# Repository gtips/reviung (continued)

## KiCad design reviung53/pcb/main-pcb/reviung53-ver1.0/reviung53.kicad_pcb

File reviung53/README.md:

# REVIUNG53  

The REVIUNG53 is 53-key keyboard.  

## Parts list  

PCB --- 1 piece  
Top plate [PCB] --- 1  
Bottom plate --- 1 piece  
Spacer 7mm --- 10 pieces  
M2 screw 4mm --- 16 pcs  
M2 screw 12mm --- 6 pcs  
M2 nut --- 2 pcs  
Rubber feet --- 6 pieces  
Diode [1N4148 SMD] --- 53 pieces  
PCB socket for switch --- 54 pcs  
Tact switch --- 1 piece  
LED [WS2812B] --- 10 pieces  
Stabilizer --- 2U x 2 , 6.25U x 1 ~  2U x 5  

ProMicro --- 1  
Con through (spring pin header 12P) --- 2  
MX compatible key switch --- 53 pcs ~ 49 (Minimum)  
MX compatible keycapset
MicroUSB cable --- 1  

### Option (Middle acrylic plate ver)
Hi-Pro acrylic frame --- 1  
Middle acrylic plate (top) --- 1  
Middle acrylic plate (bottom) --- 1  
Silicon sheet --- 1 sheet  
M2 screw 12mm --- 10 pcs  
  
[Firmware](https://github.com/qmk/qmk_firmware/tree/master/keyboards/reviung/reviung53)  
[Build guide](https://reviung.com/build-guide/)

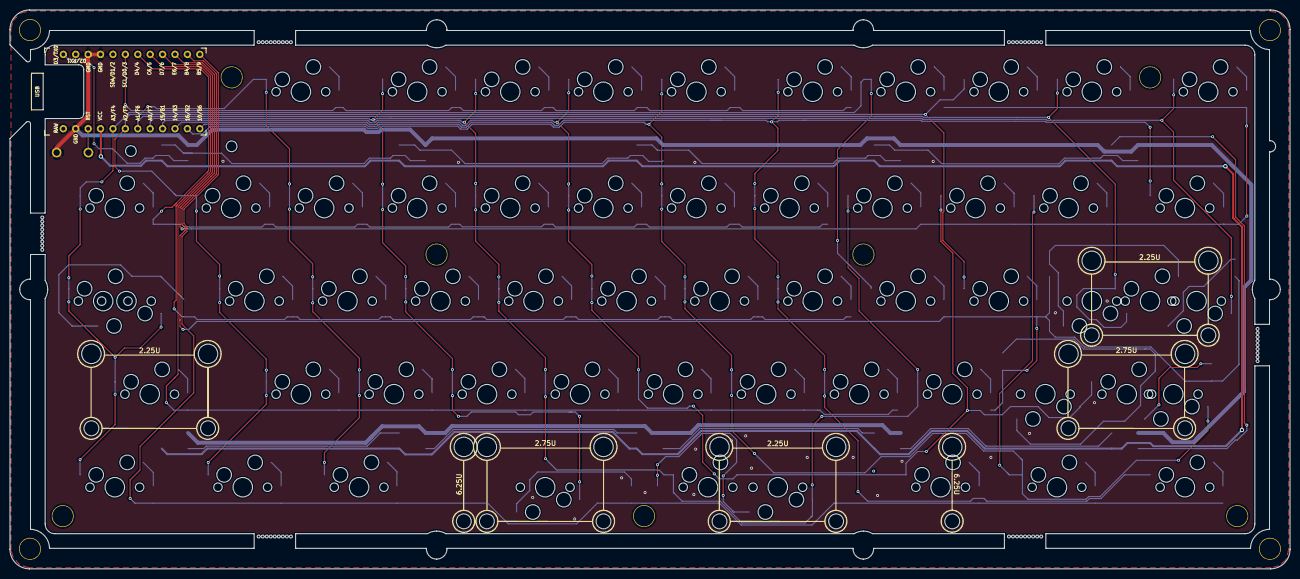
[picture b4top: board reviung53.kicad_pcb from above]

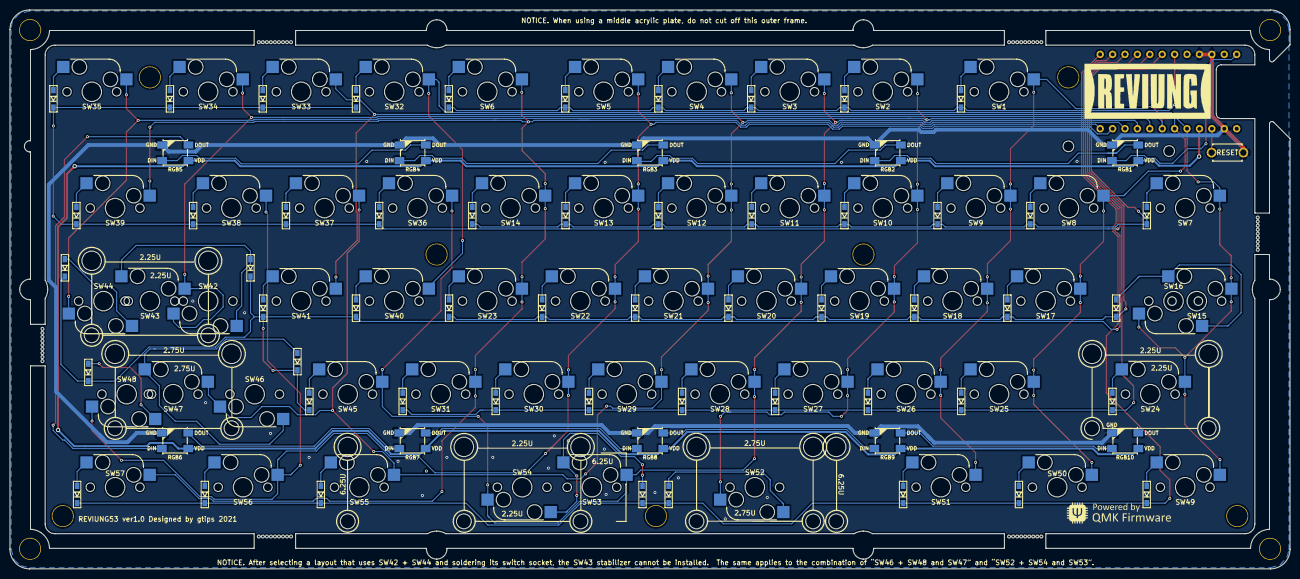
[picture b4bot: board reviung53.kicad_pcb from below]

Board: 2 copper layers, 262.0 x 114.4 mm, 130 parts (64 on the bottom side), 81 nets.

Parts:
D1, D2, D3, D4, D5, D6, D7, D8, D9, D10, D11, D12, D13, D14, D15, D16, D17, D18, D19, D20, D21, D22, D23, D24, D25, D26, D27, D28, D29, D30, D31, D32, D33, D34, D35, D36, D37, D38, D39, D40, D41, D42, D43, D44, D45, D46, D47, D48, D49, D50, D51, D52, D53: 1N4148W; D3_SMD_1side
RESET1: SW_PUSH; ResetSW_1side
RGB1, RGB2, RGB3, RGB4, RGB5, RGB6, RGB7, RGB8, RGB9, RGB10: WS2812B; LED_WS2812B_PLCC4_5.0x5.0mm_P3.2mm_BigFoot
Ref**: Val**; HOLE_2.2mm
Ref**#2: Val**; HOLE_2.2mm
SW1: 1; MXOnly-1U-Hotswap
SW2: 2; MXOnly-1U-Hotswap
SW3: 3; MXOnly-1U-Hotswap
SW4: 4; MXOnly-1U-Hotswap
SW5: 5; MXOnly-1U-Hotswap
SW6: 6; MXOnly-1U-Hotswap
SW7, SW39, SW49, SW57: 1.5U; MXOnly-1.5U-Hotswap
SW8: Q; MXOnly-1U-Hotswap
SW9: W; MXOnly-1U-Hotswap
SW10: E; MXOnly-1U-Hotswap
SW11: R; MXOnly-1U-Hotswap
SW12: T; MXOnly-1U-Hotswap
SW13: Y; MXOnly-1U-Hotswap
SW14: U; MXOnly-1U-Hotswap
SW15, SW44, SW50, SW51, SW55, SW56: 1.25U; MXOnly-1.25U-Hotswap
SW16, SW48: 1.75U; MXOnly-1.75U-Hotswap
SW17: A; MXOnly-1U-Hotswap
SW18: S; MXOnly-1U-Hotswap
SW19: D; MXOnly-1U-Hotswap
SW20: F; MXOnly-1U-Hotswap
SW21: G; MXOnly-1U-Hotswap
SW22: H; MXOnly-1U-Hotswap
SW23: J; MXOnly-1U-Hotswap
SW24, SW43: 2.25U; MXOnly-2.25U-Hotswap-ReversedStabilizers
SW25: Z; MXOnly-1U-Hotswap
SW26: X; MXOnly-1U-Hotswap
SW27: C; MXOnly-1U-Hotswap
SW28: V; MXOnly-1U-Hotswap
SW29: B; MXOnly-1U-Hotswap
SW30: N; MXOnly-1U-Hotswap
SW31: M; MXOnly-1U-Hotswap
SW32: 7; MXOnly-1U-Hotswap
SW33: 8; MXOnly-1U-Hotswap
SW34: 9; MXOnly-1U-Hotswap
SW35, SW37: 0; MXOnly-1U-Hotswap
SW36: I; MXOnly-1U-Hotswap
SW38: P; MXOnly-1U-Hotswap
SW40: K; MXOnly-1U-Hotswap
SW41: L; MXOnly-1U-Hotswap
SW42, SW46: 1U; MXOnly-1U-Hotswap
SW45: <; MXOnly-1U-Hotswap
SW47: 2.75U; MXOnly-2.75U-Hotswap-ReversedStabilizers
SW52: 2.75U; MXOnly-2.75U-Hotswap
SW53: 6.25U; MXOnly-6.25U-Hotswap-ReversedStabilizers
SW54: 2.25U; MXOnly-2.25U-Hotswap
U1: ProMicro
breakaway: Stamp_Holes_7.5mm
breakaway#2, breakaway#3, breakaway#4, breakaway#5, breakaway#6: Stamp_Holes_7.5mm

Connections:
GND: RESET1.2, RGB1.3, RGB2.3, RGB3.3, RGB4.3, RGB5.3, RGB6.3, RGB7.3, RGB8.3, RGB9.3, RGB10.3, U1.3, U1.4, U1.23
LED: RGB1.4, U1.1
unnamed: D1.2, SW1.2
unnamed: D2.2, SW2.2
unnamed: D3.2, SW3.2
unnamed: D4.2, SW4.2
unnamed: D5.2, SW5.2
unnamed: D6.2, SW6.2
unnamed: D7.2, SW7.2
unnamed: D8.2, SW8.2
unnamed: D9.2, SW9.2
unnamed: D10.2, SW10.2
unnamed: D11.2, SW11.2
unnamed: D12.2, SW12.2
unnamed: D13.2, SW13.2
unnamed: D14.2, SW14.2
unnamed: D15.2, SW17.2
unnamed: D16.2, SW18.2
unnamed: D17.2, SW19.2
unnamed: D18.2, SW20.2
unnamed: D19.2, SW21.2
unnamed: D20.2, SW22.2
unnamed: D21.2, SW23.2
unnamed: D22.2, SW15.2, SW16.2
unnamed: D23.2, SW24.2
unnamed: D24.2, SW25.2
unnamed: D25.2, SW26.2
unnamed: D26.2, SW27.2
unnamed: D27.2, SW28.2
unnamed: D28.2, SW29.2
unnamed: D29.2, SW30.2
unnamed: D30.2, SW31.2
unnamed: D31.2, SW32.2
unnamed: D32.2, SW33.2
unnamed: D33.2, SW34.2
unnamed: D34.2, SW35.2
unnamed: D35.2, SW36.2
unnamed: D36.2, SW37.2
unnamed: D37.2, SW38.2
unnamed: D38.2, SW39.2
unnamed: D39.2, SW40.2
unnamed: D40.2, SW41.2
unnamed: D41.2, SW44.2
unnamed: D42.2, SW45.2
unnamed: D43.2, SW48.2
unnamed: D44.2, SW42.2, SW43.2
unnamed: D45.2, SW46.2, SW47.2
unnamed: D46.2, SW49.2
unnamed: D47.2, SW50.2
unnamed: D48.2, SW51.2
unnamed: D49.2, SW52.2
unnamed: D50.2, SW55.2
unnamed: D51.2, SW56.2
unnamed: D52.2, SW57.2
unnamed: D53.2, SW53.2, SW54.2
unnamed: RGB1.2, RGB2.4
unnamed: RGB2.2, RGB3.4
unnamed: RGB3.2, RGB4.4
unnamed: RGB4.2, RGB5.4
unnamed: RGB5.2, RGB6.4
unnamed: RGB6.2, RGB7.4
unnamed: RGB7.2, RGB8.4
unnamed: RGB8.2, RGB9.4
unnamed: RGB9.2, RGB10.4
VCC: RGB1.1, RGB2.1, RGB3.1, RGB4.1, RGB5.1, RGB6.1, RGB7.1, RGB8.1, RGB9.1, RGB10.1, U1.21
col0: SW7.1, SW15.1, SW16.1, SW24.1, SW32.1, SW40.1, SW49.1, U1.20
col1: SW8.1, SW17.1, SW25.1, SW33.1, SW41.1, SW50.1, U1.19
col2: SW1.1, SW9.1, SW18.1, SW26.1, SW34.1, SW42.1, SW43.1, SW51.1, U1.18
col3: SW2.1, SW10.1, SW19.1, SW27.1, SW35.1, SW44.1, SW52.1, U1.17
col4: SW3.1, SW11.1, SW20.1, SW28.1, SW36.1, SW45.1, SW53.1, SW54.1, U1.16
col5: SW4.1, SW12.1, SW21.1, SW29.1, SW37.1, SW46.1, SW47.1, SW55.1, U1.15
col6: SW5.1, SW13.1, SW22.1, SW30.1, SW38.1, SW48.1, SW56.1, U1.14
col7: SW6.1, SW14.1, SW23.1, SW31.1, SW39.1, SW57.1, U1.13
reset: RESET1.1, U1.22
row0: D1.1, D2.1, D3.1, D4.1, D5.1, D6.1, U1.6
row1: D7.1, D8.1, D9.1, D10.1, D11.1, D12.1, D13.1, D14.1, U1.7
row2: D15.1, D16.1, D17.1, D18.1, D19.1, D20.1, D21.1, D22.1, U1.8
row3: D23.1, D24.1, D25.1, D26.1, D27.1, D28.1, D29.1, D30.1, U1.9
row4: D31.1, D32.1, D33.1, D34.1, D35.1, D36.1, D37.1, D38.1, U1.10
row5: D39.1, D40.1, D41.1, D42.1, D43.1, D44.1, D45.1, U1.11
row6: D46.1, D47.1, D48.1, D49.1, D50.1, D51.1, D52.1, D53.1, U1.12

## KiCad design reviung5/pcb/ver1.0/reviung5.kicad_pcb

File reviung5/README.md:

# REVIUNG5  

The REVIUNG5 is 5-key (or 4-key + Rotary Encoder) macropad.  

## Parts list  

| Qnty | Parts | Description |
| --- | --- | --- |
| 1 | PCB | Main PCB |  
| 1 | Top plate |  |
| 1 | Bottom plate |  |
| 1 | ProMicro cover plate | option |
| 3 | Acrylic spacer |  for Pro Micro cover |
| 3 | Spacer | for body |
| 6 | M2 screw 4mm |  for body |  
| 3 | M2 screw 8 - 10mm |  for Pro Micro cover |
| 3 | M2 nut |  for Pro Micro cover |
| 4 | Rubber feet |  |
| 5 | Diode [1N4148]  |  |
| 1 | Tact switch |  RESET switch |
| 4 | LED [WS2812B]  | option |
| - | - | - |
| 1 | ProMicro |  |
| 2 | Con through  | or spring pin header 12P |
| 5 (or 4) | MX compatible key switch |  |  
| 5 (or 4) | MX compatible keycap (1U) |  | 
| 1 (or 0) | Rotary Encoder | Alps EC12 series compatible | 
| 1 | MicroUSB cable |  |
  
[Firmware](https://github.com/qmk/qmk_firmware/tree/master/keyboards/reviung/reviung5)  
[Build guide](https://reviung.com/build-guide/)

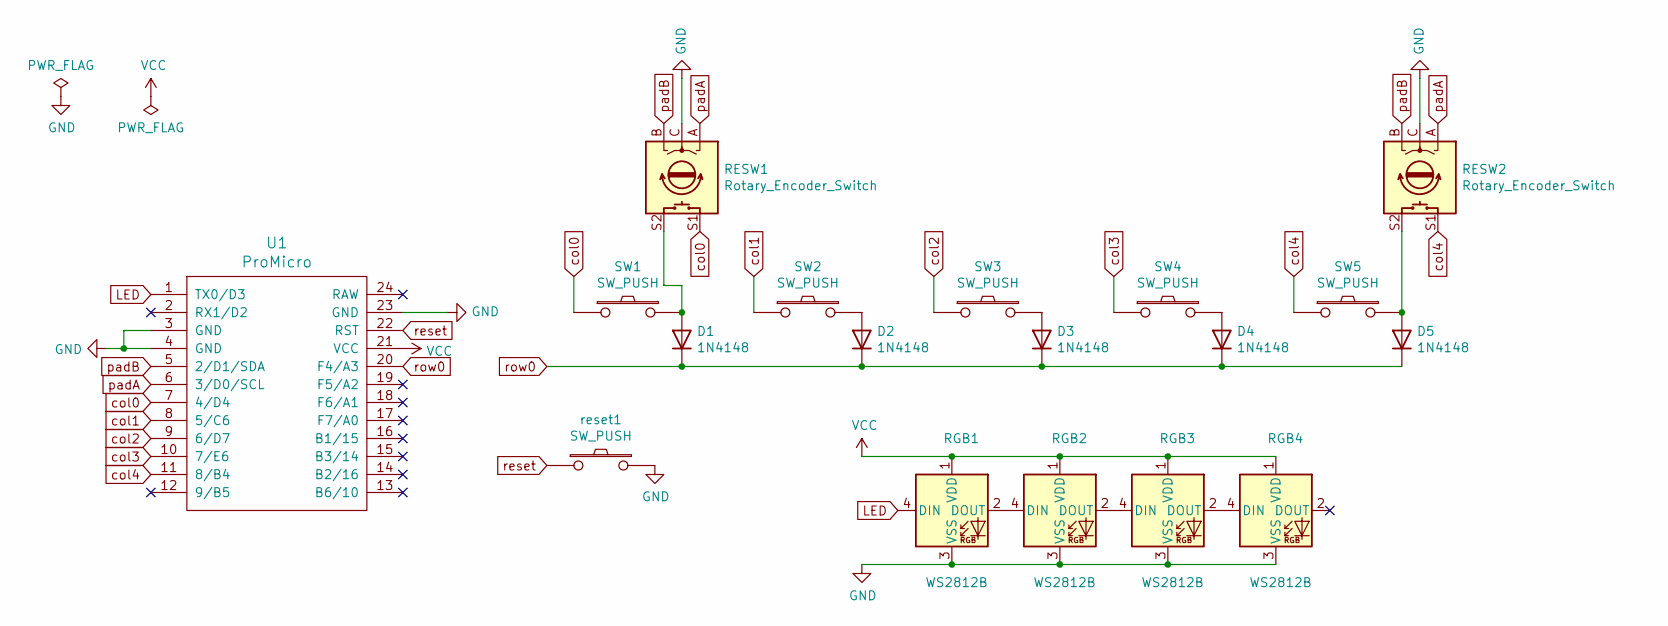
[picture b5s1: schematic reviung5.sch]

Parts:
D1, D2, D3, D4, D5: 1N4148; D3_TH_SMD_1side
RESW1, RESW2: Rotary_Encoder_Switch; RotaryEncoder_Alps_EC12E-Switch_Vertical_H20mm_CircularMoun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
RGB1, RGB2, RGB3, RGB4: WS2812B; LED_WS2812B_PLCC4_5.0x5.0mm_P3.2mm
SW1, SW5: SW_PUSH; MXOnly-1U-3pin
SW2, SW3, SW4: SW_PUSH; MXOnly-1U-NoLED
U1: ProMicro
reset1: SW_PUSH; ResetSW_TH_SMD

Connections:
GND: RESW1.C, RESW2.C, RGB1.3 (VSS), RGB2.3 (VSS), RGB3.3 (VSS), RGB4.3 (VSS), U1.3 (GND), U1.4 (GND), U1.23 (GND), reset1.2
LED: RGB1.4 (DIN), U1.1 (TX0/D3)
unnamed: D1.2 (A), RESW1.S2, SW1.2
unnamed: D2.2 (A), SW2.2
unnamed: D3.2 (A), SW3.2
unnamed: D4.2 (A), SW4.2
unnamed: D5.2 (A), RESW2.S2, SW5.2
unnamed: RGB1.2 (DOUT), RGB2.4 (DIN)
unnamed: RGB2.2 (DOUT), RGB3.4 (DIN)
unnamed: RGB3.2 (DOUT), RGB4.4 (DIN)
VCC: RGB1.1 (VDD), RGB2.1 (VDD), RGB3.1 (VDD), RGB4.1 (VDD), U1.21 (VCC)
col0: RESW1.S1, SW1.1, U1.7 (4/D4)
col1: SW2.1, U1.8 (5/C6)
col2: SW3.1, U1.9 (6/D7)
col3: SW4.1, U1.10 (7/E6)
col4: RESW2.S1, SW5.1, U1.11 (8/B4)
padA: RESW1.A, RESW2.A, U1.6 (3/D0/SCL)
padB: RESW1.B, RESW2.B, U1.5 (2/D1/SDA)
reset: U1.22 (RST), reset1.1
row0: D1.1 (K), D2.1 (K), D3.1 (K), D4.1 (K), D5.1 (K), U1.20 (F4/A3)

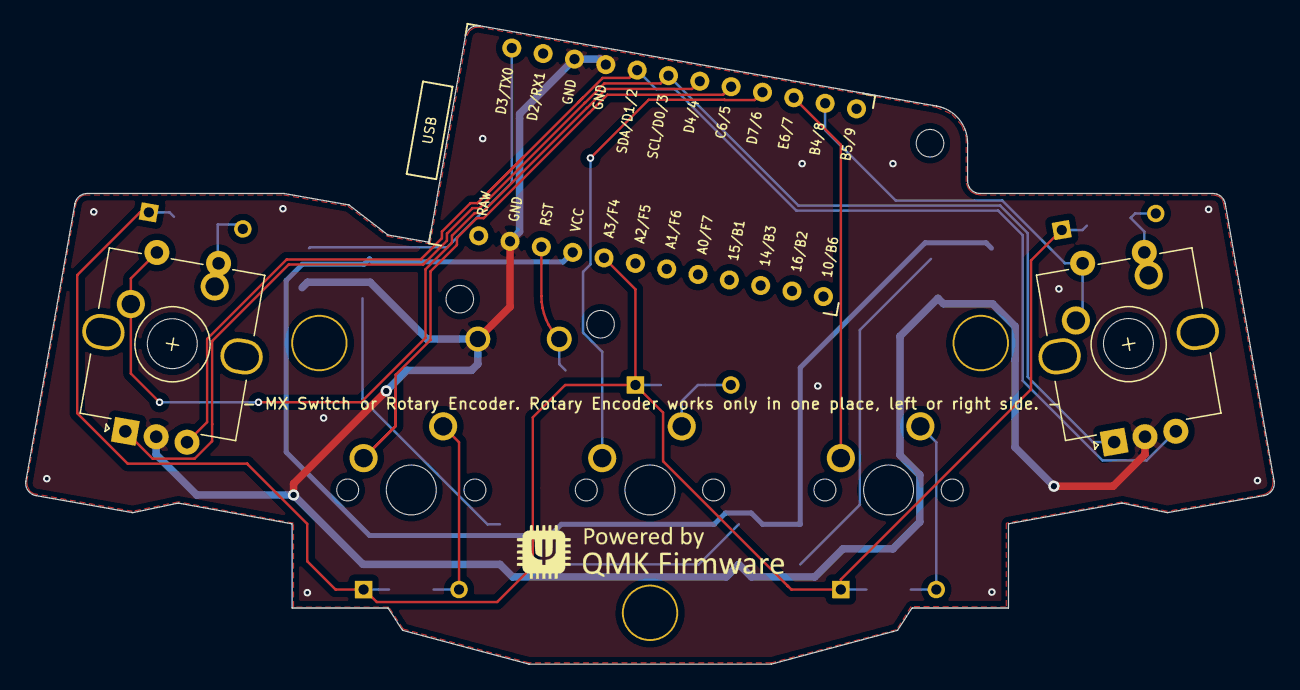
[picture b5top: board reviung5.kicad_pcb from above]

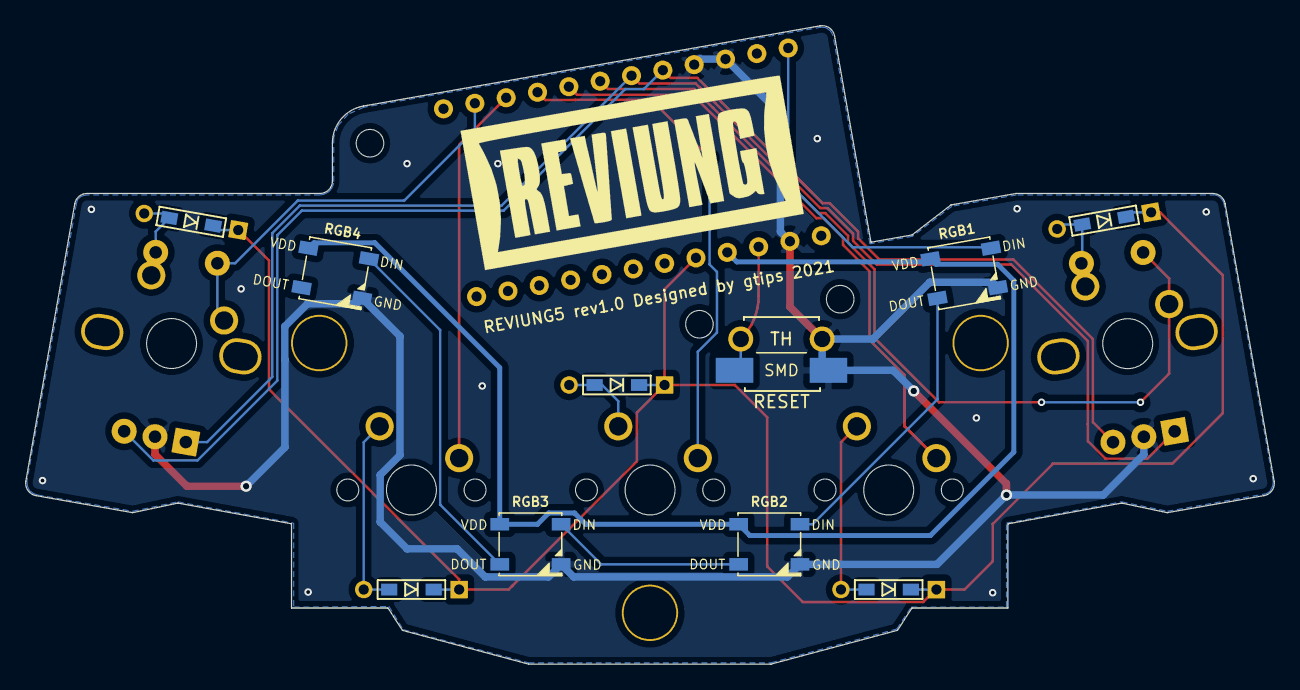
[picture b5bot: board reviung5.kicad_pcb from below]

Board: 2 copper layers, 99.7 x 51.0 mm, 21 parts (10 on the bottom side), 20 nets.

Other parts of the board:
Ref**: Val**; HOLE_2.2mm
Ref**#2, Ref**#3: Val**; HOLE_2.2mm

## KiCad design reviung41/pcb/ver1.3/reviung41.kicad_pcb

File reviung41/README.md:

# REVIUNG41  

The REVIUNG41 is 41-key column staggered keyboard.  

## Parts list  

PCB --- 1 piece  
Top plate [PCB] --- 1  
Silicon sheet --- 1 sheet  
Middle acrylic plate (top) --- 1  
Middle acrylic plate (bottom) --- 1  
Bottom plate --- 1 piece  
ProMicro protective plate --- 4 types  
Acrylic spacer --- 3 pieces  
Spacer --- 11 pieces  
M2 screw 4mm --- 22 pcs  
M2 screw 10mm --- 3 pcs  
M2 nut --- 3 pcs  
Rubber feet --- 6 pieces  
Diode [1N4148 SMD] --- 41 pieces  
PCB socket for switch --- 41 pcs  
Tact switch --- 1 piece  
LED [WS2812B] --- 11 pieces  
Stabilizer --- 1 piece  

ProMicro --- 1  
Con through (spring pin header 12P) --- 2  
MX compatible key switch --- 41 pcs  
MX compatible keycap (1U) --- 36  
Keycap (2.25U or 2U) --- 1  
Keycap (1.25U or 1U) --- 4  
MicroUSB cable --- 1  
  
[Firmware](https://github.com/qmk/qmk_firmware/tree/master/keyboards/reviung/reviung41)  
[Build guide](https://reviung.com/build-guide/391/)

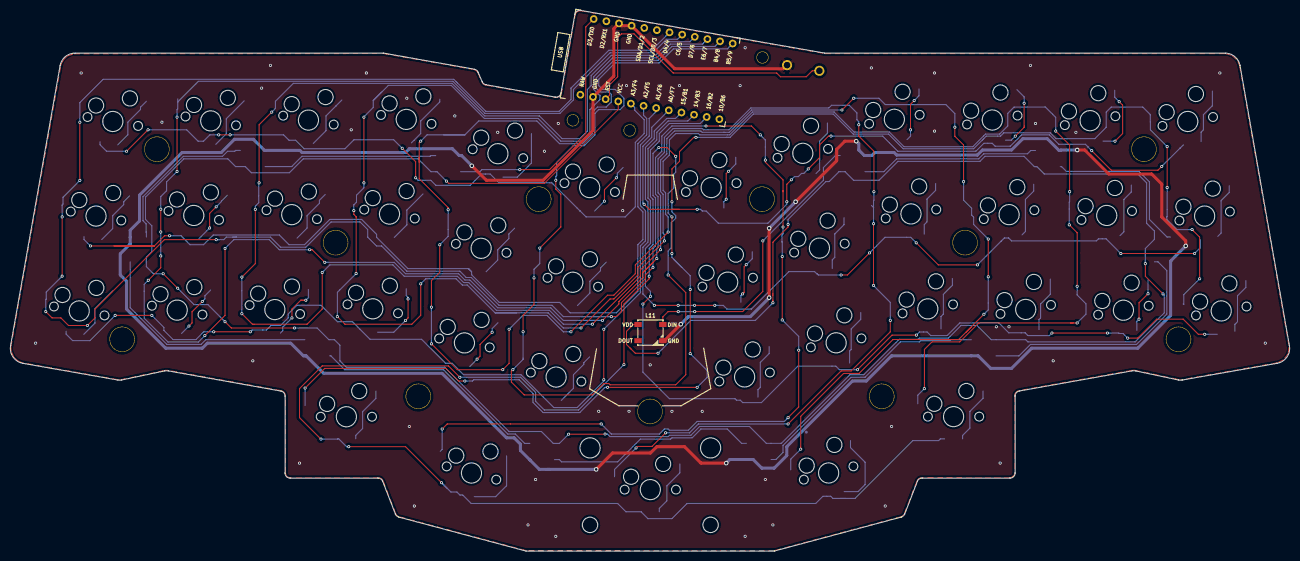
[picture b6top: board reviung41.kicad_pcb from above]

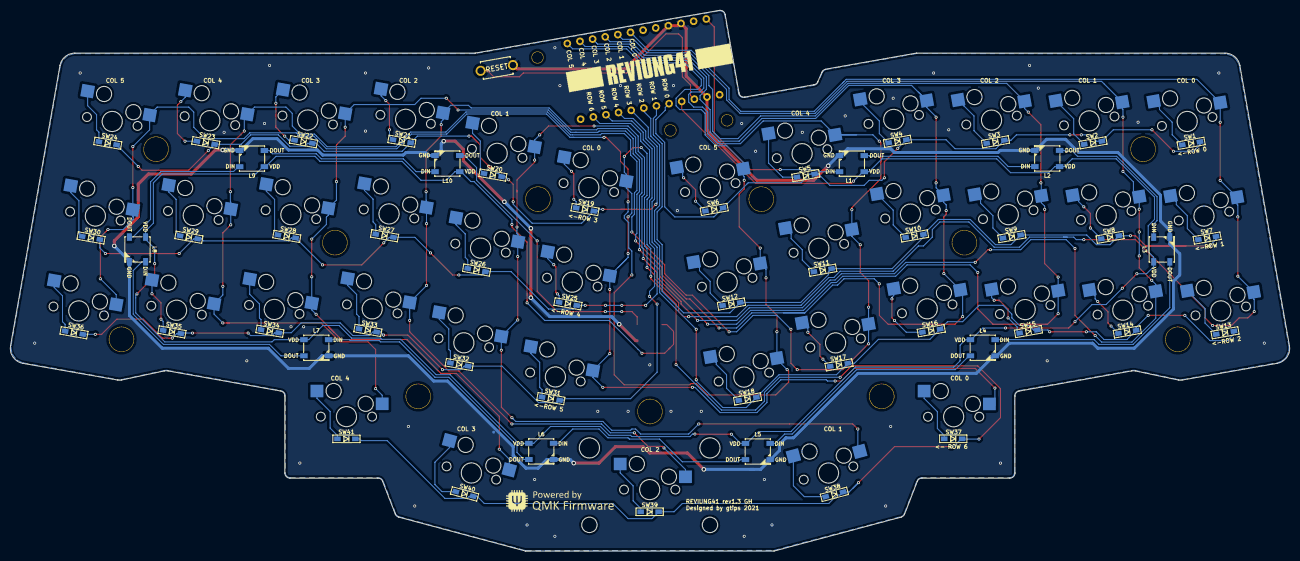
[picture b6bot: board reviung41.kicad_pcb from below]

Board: 2 copper layers, 253.3 x 107.1 mm, 109 parts (52 on the bottom side), 68 nets.

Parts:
D1, D2, D3, D4, D5, D6, D7, D8, D9, D10, D11, D12, D13, D14, D15, D16, D17, D18, D19, D20, D21, D22, D23, D24, D25, D26, D27, D28, D29, D30, D31, D32, D33, D34, D35, D36, D37, D38, D39, D40, D41: 1N4148W; D3_SMD_1side
H1: H1; HOLE
H2: H2; HOLE
H3: H3; HOLE
H4: H4; HOLE
H5: H5; HOLE
H6: H6; HOLE
H7: H7; HOLE
H8: H8; HOLE
H9: H9; HOLE
H10: H10; HOLE
H11: H11; HOLE
H12: H12; HOLE_2.2mm
H13: H13; HOLE_2.2mm
H14: H14; HOLE_2.2mm
L1, L2, L3, L4, L5, L6, L7, L8, L9, L10, L11: WS2812B; LED_WS2812B_PLCC4_5.0x5.0mm_P3.2mm
RESET1: SW_PUSH; ResetSW_1side
SW1, SW2, SW3, SW4, SW5, SW6, SW7, SW8, SW9, SW10, SW11, SW12, SW13, SW14, SW15, SW16, SW17, SW18, SW19, SW20, SW21, SW22, SW23, SW24, SW25, SW26, SW27, SW28, SW29, SW30, SW31, SW32, SW33, SW34, SW35, SW36, SW37, SW38, SW40, SW41: SW_PUSH; MXOnly-1U-Hotswap
SW39: SW_2U_PUSH; MXOnly-2U-Hotswap-ReversedStabilizers
U1: ProMicro

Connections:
GND: L1.3, L2.3, L3.3, L4.3, L5.3, L6.3, L7.3, L8.3, L9.3, L10.3, L11.3, RESET1.2, U1.3, U1.4, U1.23
LED: L1.4, U1.1
unnamed: D1.2, SW1.2
unnamed: D2.2, SW2.2
unnamed: D3.2, SW3.2
unnamed: D4.2, SW4.2
unnamed: D5.2, SW5.2
unnamed: D6.2, SW6.2
unnamed: D7.2, SW7.2
unnamed: D8.2, SW8.2
unnamed: D9.2, SW9.2
unnamed: D10.2, SW10.2
unnamed: D11.2, SW11.2
unnamed: D12.2, SW12.2
unnamed: D13.2, SW13.2
unnamed: D14.2, SW14.2
unnamed: D15.2, SW15.2
unnamed: D16.2, SW16.2
unnamed: D17.2, SW17.2
unnamed: D18.2, SW18.2
unnamed: D19.2, SW19.2
unnamed: D20.2, SW20.2
unnamed: D21.2, SW21.2
unnamed: D22.2, SW22.2
unnamed: D23.2, SW23.2
unnamed: D24.2, SW24.2
unnamed: D25.2, SW25.2
unnamed: D26.2, SW26.2
unnamed: D27.2, SW27.2
unnamed: D28.2, SW28.2
unnamed: D29.2, SW29.2
unnamed: D30.2, SW30.2
unnamed: D31.2, SW31.2
unnamed: D32.2, SW32.2
unnamed: D33.2, SW33.2
unnamed: D34.2, SW34.2
unnamed: D35.2, SW35.2
unnamed: D36.2, SW36.2
unnamed: D37.2, SW37.2
unnamed: D38.2, SW38.2
unnamed: D39.2, SW39.2
unnamed: D40.2, SW40.2
unnamed: D41.2, SW41.2
unnamed: L1.2, L2.4
unnamed: L2.2, L3.4
unnamed: L3.2, L4.4
unnamed: L4.2, L5.4
unnamed: L5.2, L6.4
unnamed: L6.2, L7.4
unnamed: L7.2, L8.4
unnamed: L8.2, L9.4
unnamed: L10.2, L11.4
unnamed: L9.2, L10.4
VCC: L1.1, L2.1, L3.1, L4.1, L5.1, L6.1, L7.1, L8.1, L9.1, L10.1, L11.1, U1.21
col0: SW1.1, SW7.1, SW13.1, SW19.1, SW25.1, SW31.1, SW37.1, U1.7
col1: SW2.1, SW8.1, SW14.1, SW20.1, SW26.1, SW32.1, SW38.1, U1.8
col2: SW3.1, SW9.1, SW15.1, SW21.1, SW27.1, SW33.1, SW39.1, U1.9
col3: SW4.1, SW10.1, SW16.1, SW22.1, SW28.1, SW34.1, SW40.1, U1.10
col4: SW5.1, SW11.1, SW17.1, SW23.1, SW29.1, SW35.1, SW41.1, U1.11
col5: SW6.1, SW12.1, SW18.1, SW24.1, SW30.1, SW36.1, U1.12
reset: RESET1.1, U1.22
row0: D1.1, D2.1, D3.1, D4.1, D5.1, D6.1, U1.20
row1: D7.1, D8.1, D9.1, D10.1, D11.1, D12.1, U1.19
row2: D13.1, D14.1, D15.1, D16.1, D17.1, D18.1, U1.18
row3: D19.1, D20.1, D21.1, D22.1, D23.1, D24.1, U1.17
row4: D25.1, D26.1, D27.1, D28.1, D29.1, D30.1, U1.16
row5: D31.1, D32.1, D33.1, D34.1, D35.1, D36.1, U1.15
row6: D37.1, D38.1, D39.1, D40.1, D41.1, U1.14

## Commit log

2019-07-12 add: pcb
2019-08-27 add pcb, svg and image
2019-09-25 add reviung39/pcb-top-plate/gerber.zip
2019-09-25 add reviung34split
2019-09-30 add reviung34split/image/REVIUNG34.jpg
2019-09-30 add reviung34split/README.md
2019-11-12 update reviung34split pcb file
2019-12-05 add reviung39/acrylic-plate/ and reviung39s/acrylic-plate/
2019-12-12 add reviung39/acrylic-plate/lower-middle-plate/README.md
2019-12-12 add reviung39/image/REVIUNG39mdp-x.jpg
2019-12-14 add reviung39/acrylic-plate.zip
2020-01-06 add reviung41
2020-01-21 update reviung41/acrylic-plate/upper-middle-plate/reviung41-upper-middle-plate
2020-02-09 add reviung41/image/ some images
2020-02-13 add README.md
2020-02-13 reviung41/image/reviung41-07.jpg, reviung41-08.jpg
2020-03-04 add reviung-stand
2020-03-04 update reviung-stand files
2020-07-16 add reviung61
2020-07-16 update reviung61/pcb-top-plate-ALPS/
2020-08-24 remove REVIUNG-STAND
2020-08-25 add reviung33
2020-08-25 upodate /README.md
2020-08-25 update reviung/acrylic-plate/
2020-08-27 add reviung39Mk-II
2020-11-13 add REVIUNG34 Mk-II
2021-01-05 Adding 3d model and stl for reviung39Mkii case
2021-04-19 add reviung41 top and bottom plate files
2021-04-19 add reviung41 top plate dwg file
2021-04-25 add new reviung34
2021-04-25 add gerver_r34_v1.zip
2021-04-26 add reviung34/acrylic-plate/bottom-plate/reviung34-bottom-plate-2mm-ver1.dxf
2021-04-28 Create fr4 bottom plate for reviung41
2021-05-04 fix README.md
2021-05-25 update reviung39_Mk-II/acrylic-plate/
2021-05-25 update reviung34/acrylic-plate/
2021-05-25 update reviung41/acrylic-plate/
2021-05-25 update reviung41/pcb/ver1.3 and reviung41/pcb-top-plate/ver1.3/
2021-06-29 fix reviung5/README.md
2021-11-15 Fix link to reviung39 mk-II in readme
    Minor tweak to documentation.
2021-12-02 add: reviung53/
2021-12-03 add: reviung53/acrylic-plate/mcu-cover-ver1.0/
2021-12-06 add: reviung53/acrylic-plate/for-middle-plate/, /for-stacked-acrylic-case/
2021-12-08 renamed folder name
2022-01-20 add reviung53/acrylic-plate/for-stacked-acrylic-case/Assembly_drawing.jpg
2022-01-20 Fixed for-middle-plate directory name
2022-01-20 fixed README.md
2022-03-31 RJ45_NONAME_8P8C_Horizontal
    Redone with very common RJ45_NONAME_8P8C_Horizontal socket's footprint and KiCad 6.0.4.
    https://aliexpress.ru/item/32774556179.html
    https://aliexpress.ru/item/4001295248605.html
    https://aliexpress.ru/item/32694863099.html
    https://aliexpress.ru/item/32902228456.html
2022-06-29 Add KiCad 6 project for reviung41
2022-06-29 Cleanup zero length and redundant tracks
2023-04-19 Fix firmware links in readme
2023-04-19 Fix reviung53 firmware link
2023-04-19 Fix firmware link for reviung33
2023-04-19 Fix firmware link for reviung34
2023-04-19 Fix firmware link for reviung34 split
2023-04-19 fix firmware link for reviung34 split mkii
2023-04-19 Fix firmware link for reviung39
2023-04-19 Fix firmware link for reviung39 mkii
2023-04-19 fix firmware link for reviung39s
2023-04-19 fix firmware link for reviung41
2023-04-19 fix firmware link for reviung5
2023-04-19 fix firmware link for reviung53
2023-04-19 Add firmware link for reviung61
2024-08-05 add reviung46
2024-08-20 add new file
2024-09-25 clean old files
